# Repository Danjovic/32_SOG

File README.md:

# 32_SOG
32 Shades of Grey - NTSC Grayscale generator

This project implements a low cost portable NTSC video pattern generator for testing monochrome video systems regarding gain and resolution. 
The circuit provides a video output with voltage and impedance according with the RS-170 standard. 
A CR2025 coin cell powers the circuit that it is automatically activated when the output plug is connected.

**Environment:**
  * Compilation: AVR Studio 4 
  * Circuit Board: Eagle 6.0 or above
  * Spreadsheets: OpenOffice

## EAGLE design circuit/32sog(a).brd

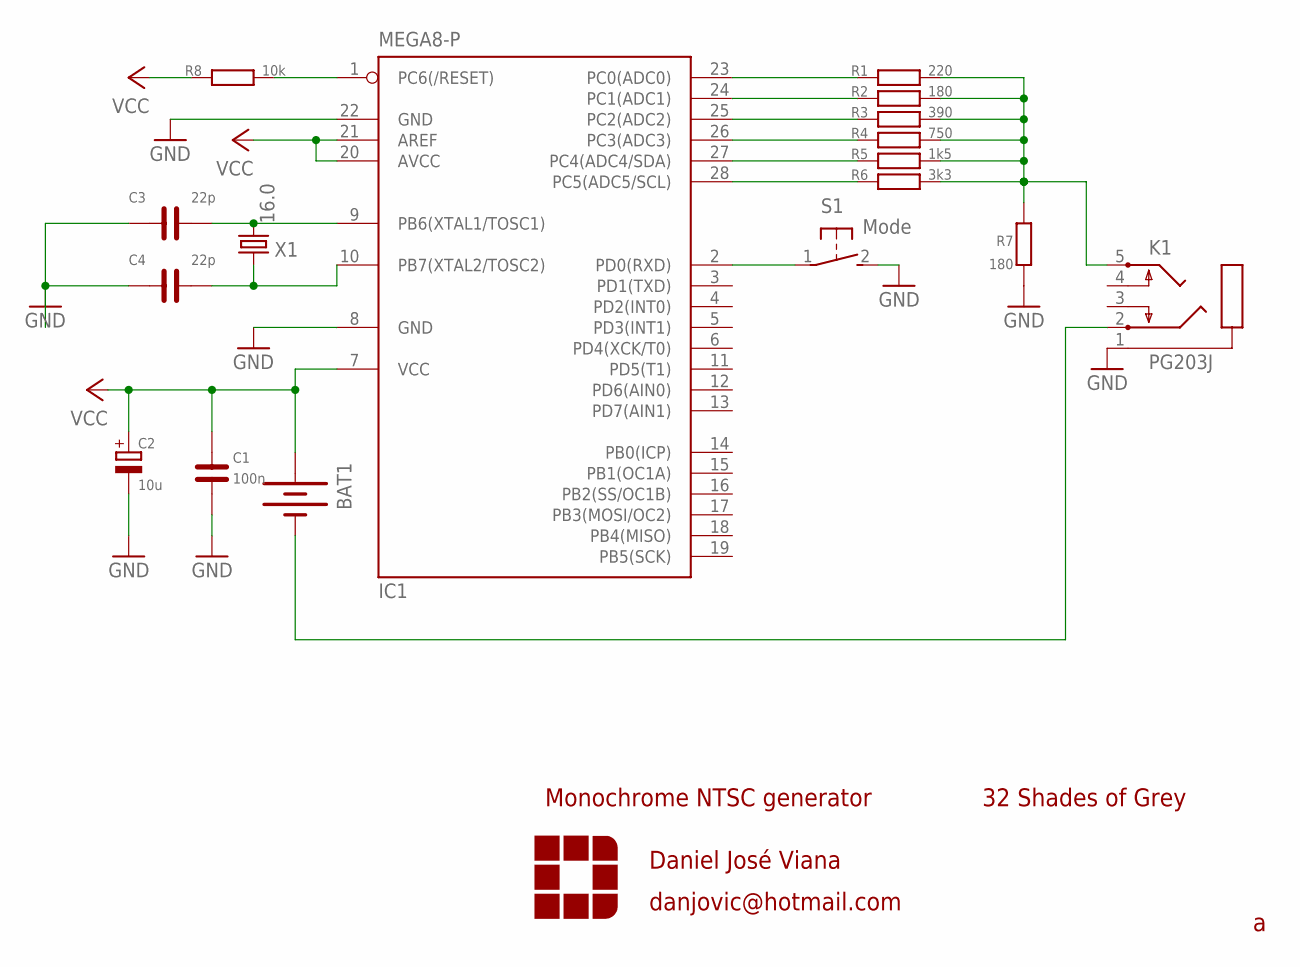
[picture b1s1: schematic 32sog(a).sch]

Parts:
BAT1: BATTERY20PTH; BATTCOM_20MM_PTH
C1: 100n; C050-024X044
C2: 10u; E2-4_LARGEPADS
C3, C4: 22p; C050-024X044
IC1: MEGA8-P; DIL28-3
K1: PG203J
R1: 220; 0207/7
R2, R7: 180; 0207/7
R3: 390; 0207/7
R4: 750; 0207/7
R5: 1k5; 0207/7
R6: 3k3; 0207/7
R8: 10k; 0207/7
S1: Mode; B3F-31XX
X1: 16.0; HC49/S

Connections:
GND: C1.1, C2.-, C3.1, C4.1, IC1.8 (GND), IC1.22 (GND), K1.1, R7.2, S1.2 (S)
unnamed: IC1.23 (PC0(ADC0)), R1.1
unnamed: IC1.25 (PC2(ADC2)), R3.1
unnamed: IC1.1 (PC6(/RESET)), R8.2
unnamed: IC1.27 (PC4(ADC4/SDA)), R5.1
unnamed: IC1.24 (PC1(ADC1)), R2.1
unnamed: IC1.26 (PC3(ADC3)), R4.1
unnamed: IC1.28 (PC5(ADC5/SCL)), R6.1
unnamed: C3.2, IC1.9 (PB6(XTAL1/TOSC1)), X1.2
unnamed: BAT1.2 (-), K1.2
unnamed: K1.5, R1.2, R2.2, R3.2, R4.2, R5.2, R6.2, R7.1
unnamed: C4.2, IC1.10 (PB7(XTAL2/TOSC2)), X1.1
unnamed: IC1.2 (PD0(RXD)), S1.1
VCC: BAT1.1 (+), C1.2, C2.+, IC1.7 (VCC), IC1.20 (AVCC), IC1.21 (AREF), R8.1

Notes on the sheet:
Daniel José Viana
danjovic@hotmail.com
32 Shades of Grey
Monochrome NTSC generator

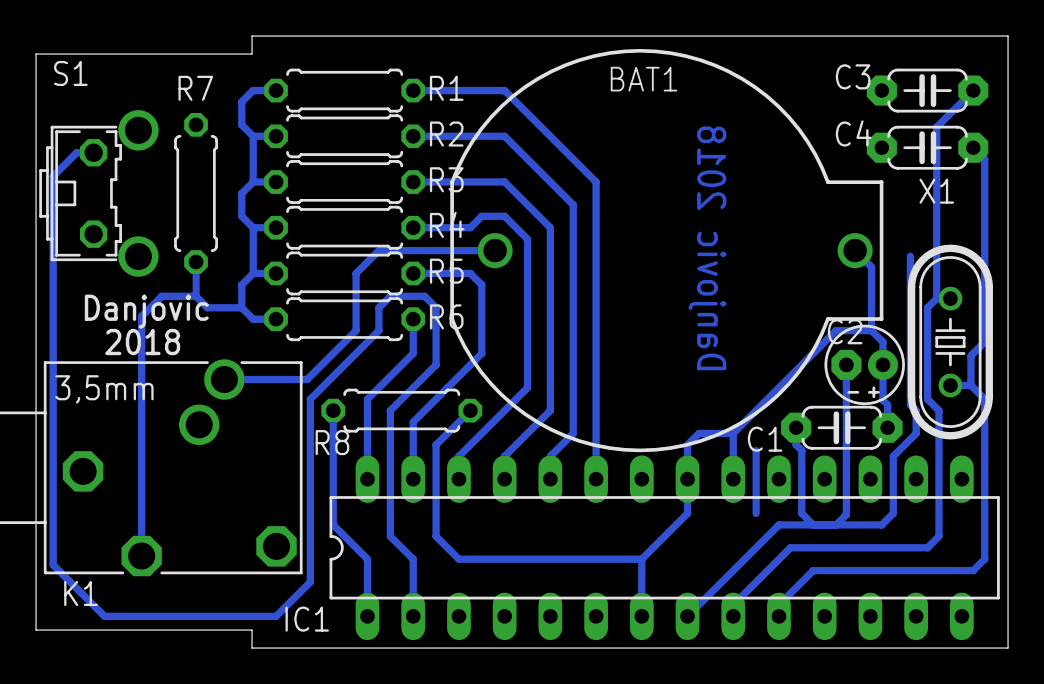
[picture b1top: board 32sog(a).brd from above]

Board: 2 copper layers, 54.0 x 34.0 mm, 18 parts (0 on the bottom side), 14 nets.

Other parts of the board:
U$1: TIC_TAC_INSET

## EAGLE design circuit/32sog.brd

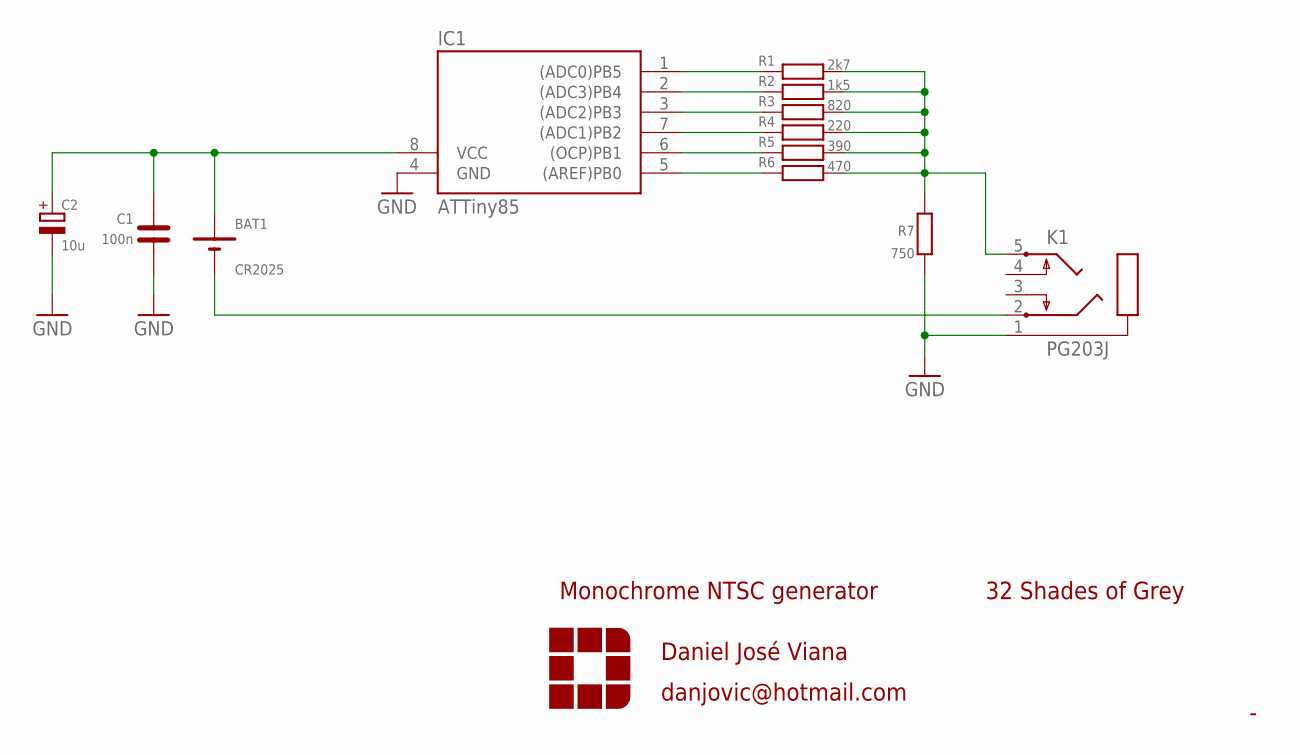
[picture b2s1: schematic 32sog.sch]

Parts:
BAT1: CR2025; CR2032-1GJ00245
C1: 100n; C050-024X044
C2: 10u; E2-4_LARGEPADS
IC1: ATTiny85; DIL08
K1: PG203J
R1: 2k7; 0207/7
R2: 1k5; 0207/7
R3: 820; 0207/7
R4: 390; 0207/7
R5: 220; 0207/7
R6: 470; 0207/7
R7: 750; 0207/7

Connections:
GND: C1.1, C2.-, IC1.4 (GND), K1.1, R7.2
unnamed: IC1.1 ((ADC0)PB5), R1.1
unnamed: IC1.3 ((ADC2)PB3), R3.1
unnamed: BAT1.PLUS, C1.2, C2.+, IC1.8 (VCC)
unnamed: IC1.6 ((OCP)PB1), R5.1
unnamed: IC1.2 ((ADC3)PB4), R2.1
unnamed: IC1.7 ((ADC1)PB2), R4.1
unnamed: IC1.5 ((AREF)PB0), R6.1
unnamed: K1.5, R1.2, R2.2, R3.2, R4.2, R5.2, R6.2, R7.1
unnamed: BAT1.MINUS, K1.2

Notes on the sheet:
Daniel José Viana
danjovic@hotmail.com
32 Shades of Grey
Monochrome NTSC generator

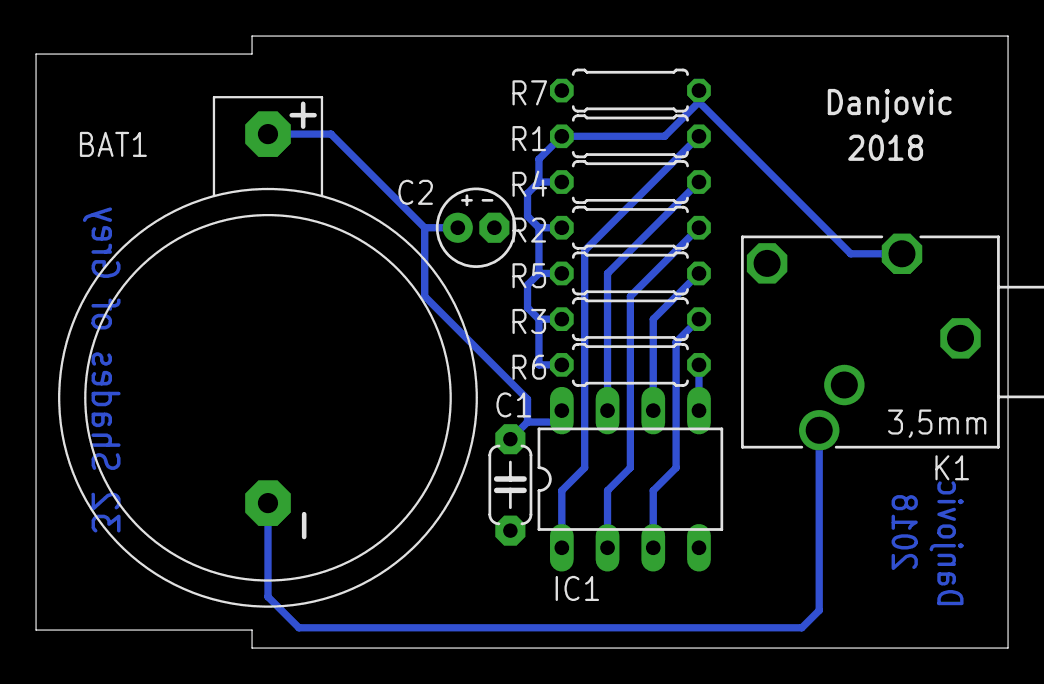
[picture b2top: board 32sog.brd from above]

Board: 2 copper layers, 54.0 x 34.0 mm, 13 parts (0 on the bottom side), 10 nets.

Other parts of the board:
U$1: TIC_TAC_INSET

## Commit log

2018-04-27 Repository creation
2018-04-27 Added schematic
2018-05-02 Circuit board for a Tic Tac mint box
2018-05-02 Cycle count ok, Yet to be tested in real hardware
2018-05-04 Added spreadsheet for calculation of resitors
2018-05-04 ATmega328 experimental version
    Experimental version, uses the ATMega328 with 16MHz crystal, aka Arduino Uno board.
2018-05-04 ATMegaxx8 board version
2018-05-05 Cleanup and bug correction, version for ATMegaxx8
2018-05-14 Added pull-up resistor on RESET line

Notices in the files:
parts and their libraries:
SparkFun-Electromechanical: Licensing: Creative Commons ShareAlike 4.0 International - https://creativecommons.org/licenses/by-sa/4.0
